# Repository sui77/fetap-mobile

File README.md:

# fetap-mobile
Turn your old Fernsprechtischapparat FeTAp 611 (or any other rotary dial phone) into a mobile phone. 

## Bom
 - FeTAp 611 rotary dial phone
 - Arduino Pro Mini
 - sim800l GSM module
 - TP4056 lithium battery charger module with protection
 - 18560 type lithium battery
 - 3V-35V step up boost converter
 - L293D H-Bridge

## Software
 - [Rotary-Dial](https://github.com/markfickett/Rotary-Dial) library
 - Arduino sketch from this repository
 
##

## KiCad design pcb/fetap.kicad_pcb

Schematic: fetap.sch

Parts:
A1: Arduino_Nano_v3.x; Arduino_Nano
Battery1: Battery; JST_EH_B2B-EH-A_1x02_P2.50mm_Vertical
Charger1: charger
Dial1: Dial; JST_EH_B4B-EH-A_1x04_P2.50mm_Vertical
Hook1: hook switch; cradleswitch
J1: Bell; JST_EH_B2B-EH-A_1x02_P2.50mm_Vertical
Power1: VIN; JST_EH_B2B-EH-A_1x02_P2.50mm_Vertical
SW1: SW_Push; SW_PUSH_6mm
StepUpModule1: stepup
U2: L293D; DIP-16_W7.62mm
U3: hoerer; suat
sim800l1: sim800l

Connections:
+5V: A1.27, Charger1.3 (OUT+), StepUpModule1.1 (IN+), U2.16 (VCC1), sim800l1.2 (VCC)
GND: A1.4, A1.29, Charger1.2 (IN-), Charger1.4 (OUT-), Dial1.1, Dial1.2, Power1.2, SW1.1, StepUpModule1.2 (IN-), StepUpModule1.4 (OUT-), U2.4 (GND), U2.5 (GND), U2.9 (EN3,4), U2.12 (GND), U2.13 (GND), sim800l1.6 (GND)
unnamed: A1.6, Dial1.4
unnamed: A1.7, Dial1.3
unnamed: A1.9, sim800l1.11 (DTR)
unnamed: A1.10, sim800l1.12 (RING)
unnamed: A1.12, sim800l1.4 (RXD)
unnamed: A1.23, Hook1.1 (a)
unnamed: A1.24, Hook1.3 (c)
unnamed: A1.25, U2.7 (2A)
unnamed: A1.26, U2.2 (1A)
unnamed: Battery1.1, Charger1.5 (B+)
unnamed: Battery1.2, Charger1.6 (B-)
unnamed: Charger1.1 (IN+), Power1.1
unnamed: J1.1, U2.3 (1Y)
unnamed: J1.2, U2.6 (2Y)
unnamed: SW1.2, sim800l1.3 (RST)
unnamed: StepUpModule1.3 (OUT+), U2.8 (VCC2)
unnamed: U3.1 (Mic+), sim800l1.10 (MIC+)
unnamed: U3.2 (Mic-), sim800l1.9 (MIC_-)
unnamed: U3.3 (Spk+), sim800l1.8 (SPK+)
unnamed: U3.4 (Spk-), sim800l1.7 (SPK-)

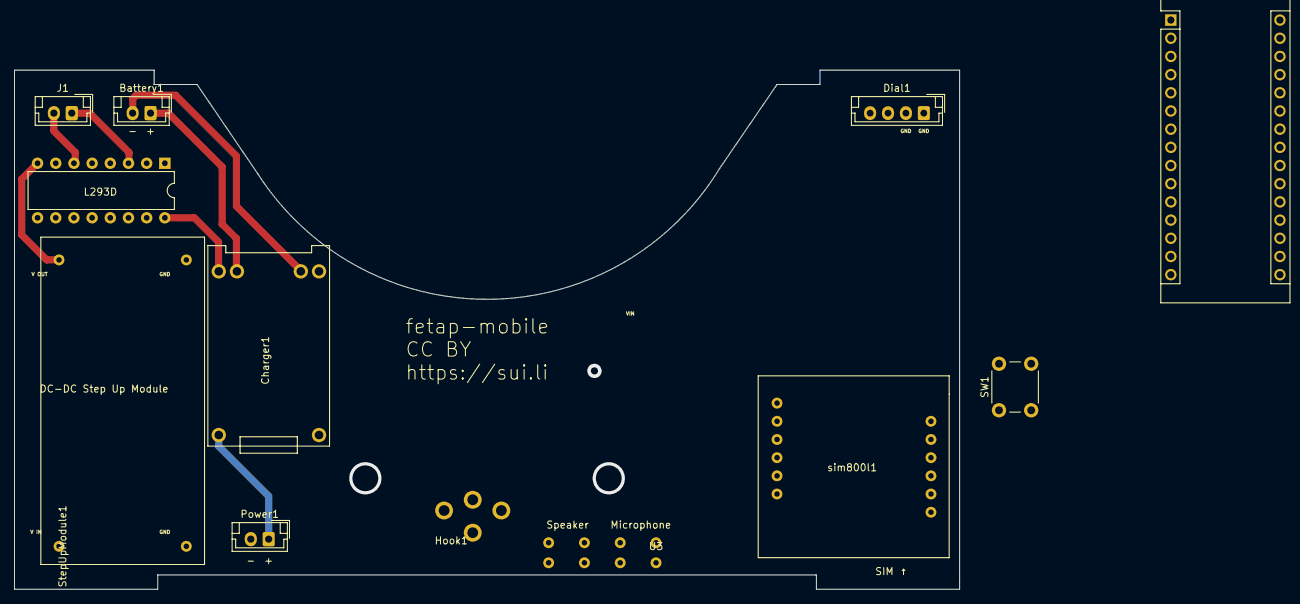
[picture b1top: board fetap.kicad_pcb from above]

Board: 2 copper layers, 132.0 x 72.5 mm, 12 parts (0 on the bottom side), 22 nets.

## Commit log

2017-03-11 initial, wip
2017-03-11 rename main ino file
2019-08-20 Enable ringing
    Resolves https://github.com/sui77/rotary-sim800/issues/1
2021-05-15 adding pcb
2021-05-22 battery holder

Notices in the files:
pcb/fetap.kicad_pcb:
CC BY
https://sui.li
